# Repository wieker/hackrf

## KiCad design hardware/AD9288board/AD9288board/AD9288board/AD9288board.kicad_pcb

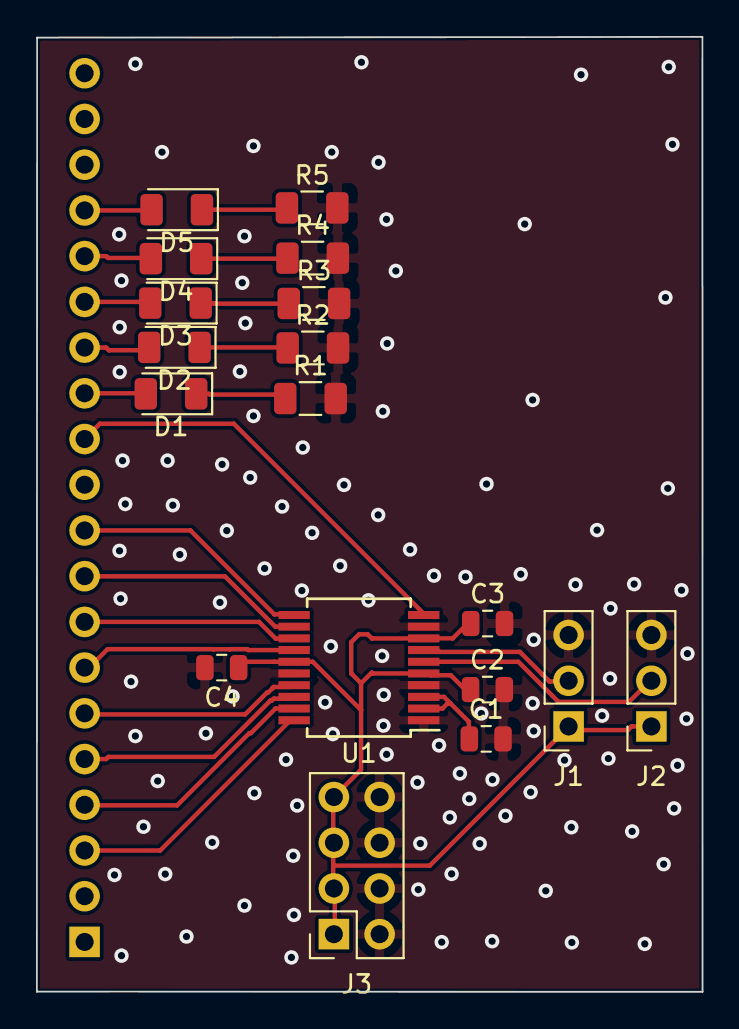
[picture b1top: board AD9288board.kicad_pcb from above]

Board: 2 copper layers, 37.0 x 53.0 mm, 19 parts (1 on the bottom side), 24 nets.

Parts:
C1, C2, C3, C4: 0.1uF; C_0805_2012Metric
D1, D2, D3, D4, D5: LED; LED_1206_3216Metric
J1, J2: Conn_01x03_Male; PinSocket_1x03_P2.54mm_Vertical
J3: Conn_02x04_Odd_Even; PinSocket_2x04_P2.54mm_Vertical
J4: Conn_01x20_Female; PinSocket_1x20_P2.54mm_Horizontal
R1, R2, R3, R4, R5: 10 kOhm; R_1206_3216Metric
U1: AD9283; SSOP-20_5.3x7.2mm_P0.65mm

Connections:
+3V3: C2.1, C3.1, C4.1, J1.1, J2.1, J3.1, J3.3, J3.5, J3.7, U1.5, U1.8, U1.15
GND: C1.2, C2.2, C3.2, C4.2, J1.3, J2.3, J3.2, J3.4, J3.6, J3.8, R1.2, R2.2, R3.2, R4.2, R5.2, U1.1, U1.4, U1.9, U1.16
unnamed: C1.1, U1.2, U1.3
unnamed: D1.1, R1.1
unnamed: D1.2, J4.13
unnamed: D2.1, R2.1
unnamed: D2.2, J4.14
unnamed: D3.1, R3.1
unnamed: D3.2, J4.15
unnamed: D4.1, R4.1
unnamed: D4.2, J4.16
unnamed: D5.1, R5.1
unnamed: D5.2, J4.17
unnamed: J1.2, U1.7
unnamed: J2.2, U1.6
unnamed: J4.3, U1.20
unnamed: J4.4, U1.19
unnamed: J4.5, U1.18
unnamed: J4.6, U1.17
unnamed: J4.7, U1.14
unnamed: J4.8, U1.13
unnamed: J4.9, U1.12
unnamed: J4.10, U1.11
unnamed: J4.12, U1.10

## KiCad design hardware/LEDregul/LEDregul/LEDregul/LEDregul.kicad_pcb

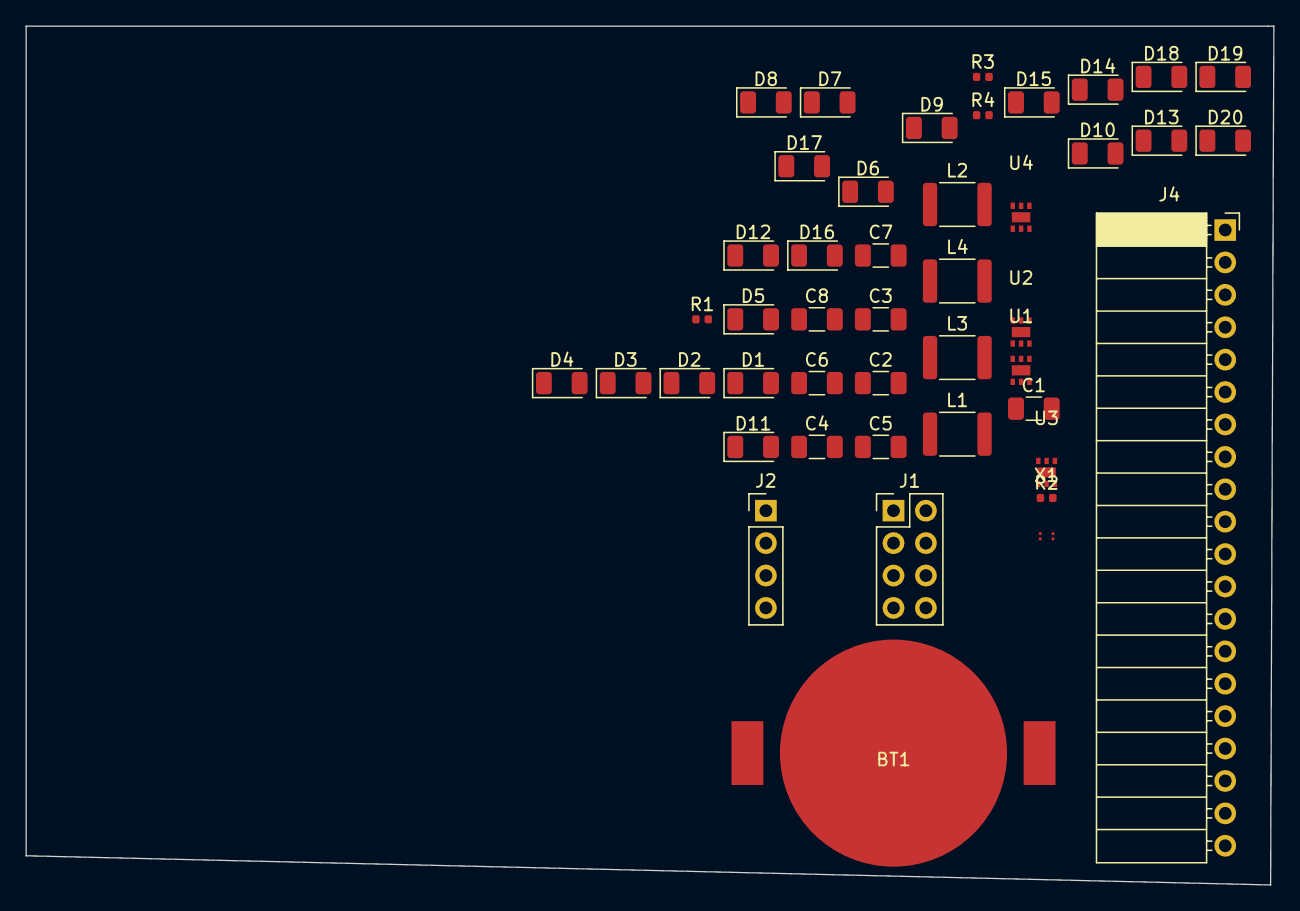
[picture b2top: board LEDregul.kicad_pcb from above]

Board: 2 copper layers, 97.8 x 67.3 mm, 45 parts (0 on the bottom side), 36 nets, no tracks yet.

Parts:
BT1: Battery_Cell; CR2032
C1, C3, C4, C7: 1uF; C_1206_3216Metric
C2, C5, C6, C8: 10uF; C_1206_3216Metric
D1, D2, D3, D4, D5, D6, D7, D8, D9, D10, D11, D12, D13, D14, D15, D16, D17, D18, D19, D20: LED; LED_1206_3216Metric
J1: Conn_02x04_Odd_Even; PinHeader_2x04_P2.54mm_Vertical
J2: Conn_01x04_Male; PinHeader_1x04_P2.54mm_Vertical
J4: Conn_01x20_Female; PinSocket_1x20_P2.54mm_Horizontal
L1, L2, L3, L4: L; L_1812_4532Metric
R1, R2, R3, R4: R; R_0402_1005Metric
U1, U2, U3, U4: FAN5341
X1: SiT1534

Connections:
+3V3: C2.1, C5.1, C6.1, C8.1, J1.2, J1.4, J1.6, J1.8, J2.3, J2.4, L1.1, L2.1, L3.1, L4.1, U1.2, U2.2, U3.2, U4.2, X1.4
C1: J4.8, U4.3
C2: J4.9, U3.3
C3: J4.10, U2.3
GND: BT1.2, C1.2, C2.2, C3.2, C4.2, C5.2, C6.2, C7.2, C8.2, J1.1, J1.3, J1.5, J1.7, R1.2, R2.2, R3.2, R4.2, U1.6, U2.6, U3.6, U4.6, X1.2
unnamed: BT1.1, J2.1, J2.2
unnamed: C1.1, D1.2, U1.1
unnamed: C3.1, D6.2, U2.1
unnamed: C4.1, D11.2, U3.1
unnamed: C7.1, D16.2, U4.1
unnamed: D1.1, D2.2
unnamed: D2.1, D3.2
unnamed: D3.1, D4.2
unnamed: D4.1, D5.2
unnamed: D5.1, R1.1, U1.4
unnamed: D6.1, D7.2
unnamed: D7.1, D8.2
unnamed: D8.1, D9.2
unnamed: D10.1, R2.1, U2.4
unnamed: D9.1, D10.2
unnamed: D11.1, D12.2
unnamed: D12.1, D13.2
unnamed: D13.1, D14.2
unnamed: D14.1, D15.2
unnamed: D15.1, R3.1, U3.4
unnamed: D16.1, D17.2
unnamed: D17.1, D18.2
unnamed: D18.1, D19.2
unnamed: D19.1, D20.2
unnamed: D20.1, R4.1, U4.4
unnamed: J4.11, X1.3
unnamed: J4.17, U1.3
unnamed: L1.2, U1.5
unnamed: L2.2, U2.5
unnamed: L3.2, U3.5
unnamed: L4.2, U4.5

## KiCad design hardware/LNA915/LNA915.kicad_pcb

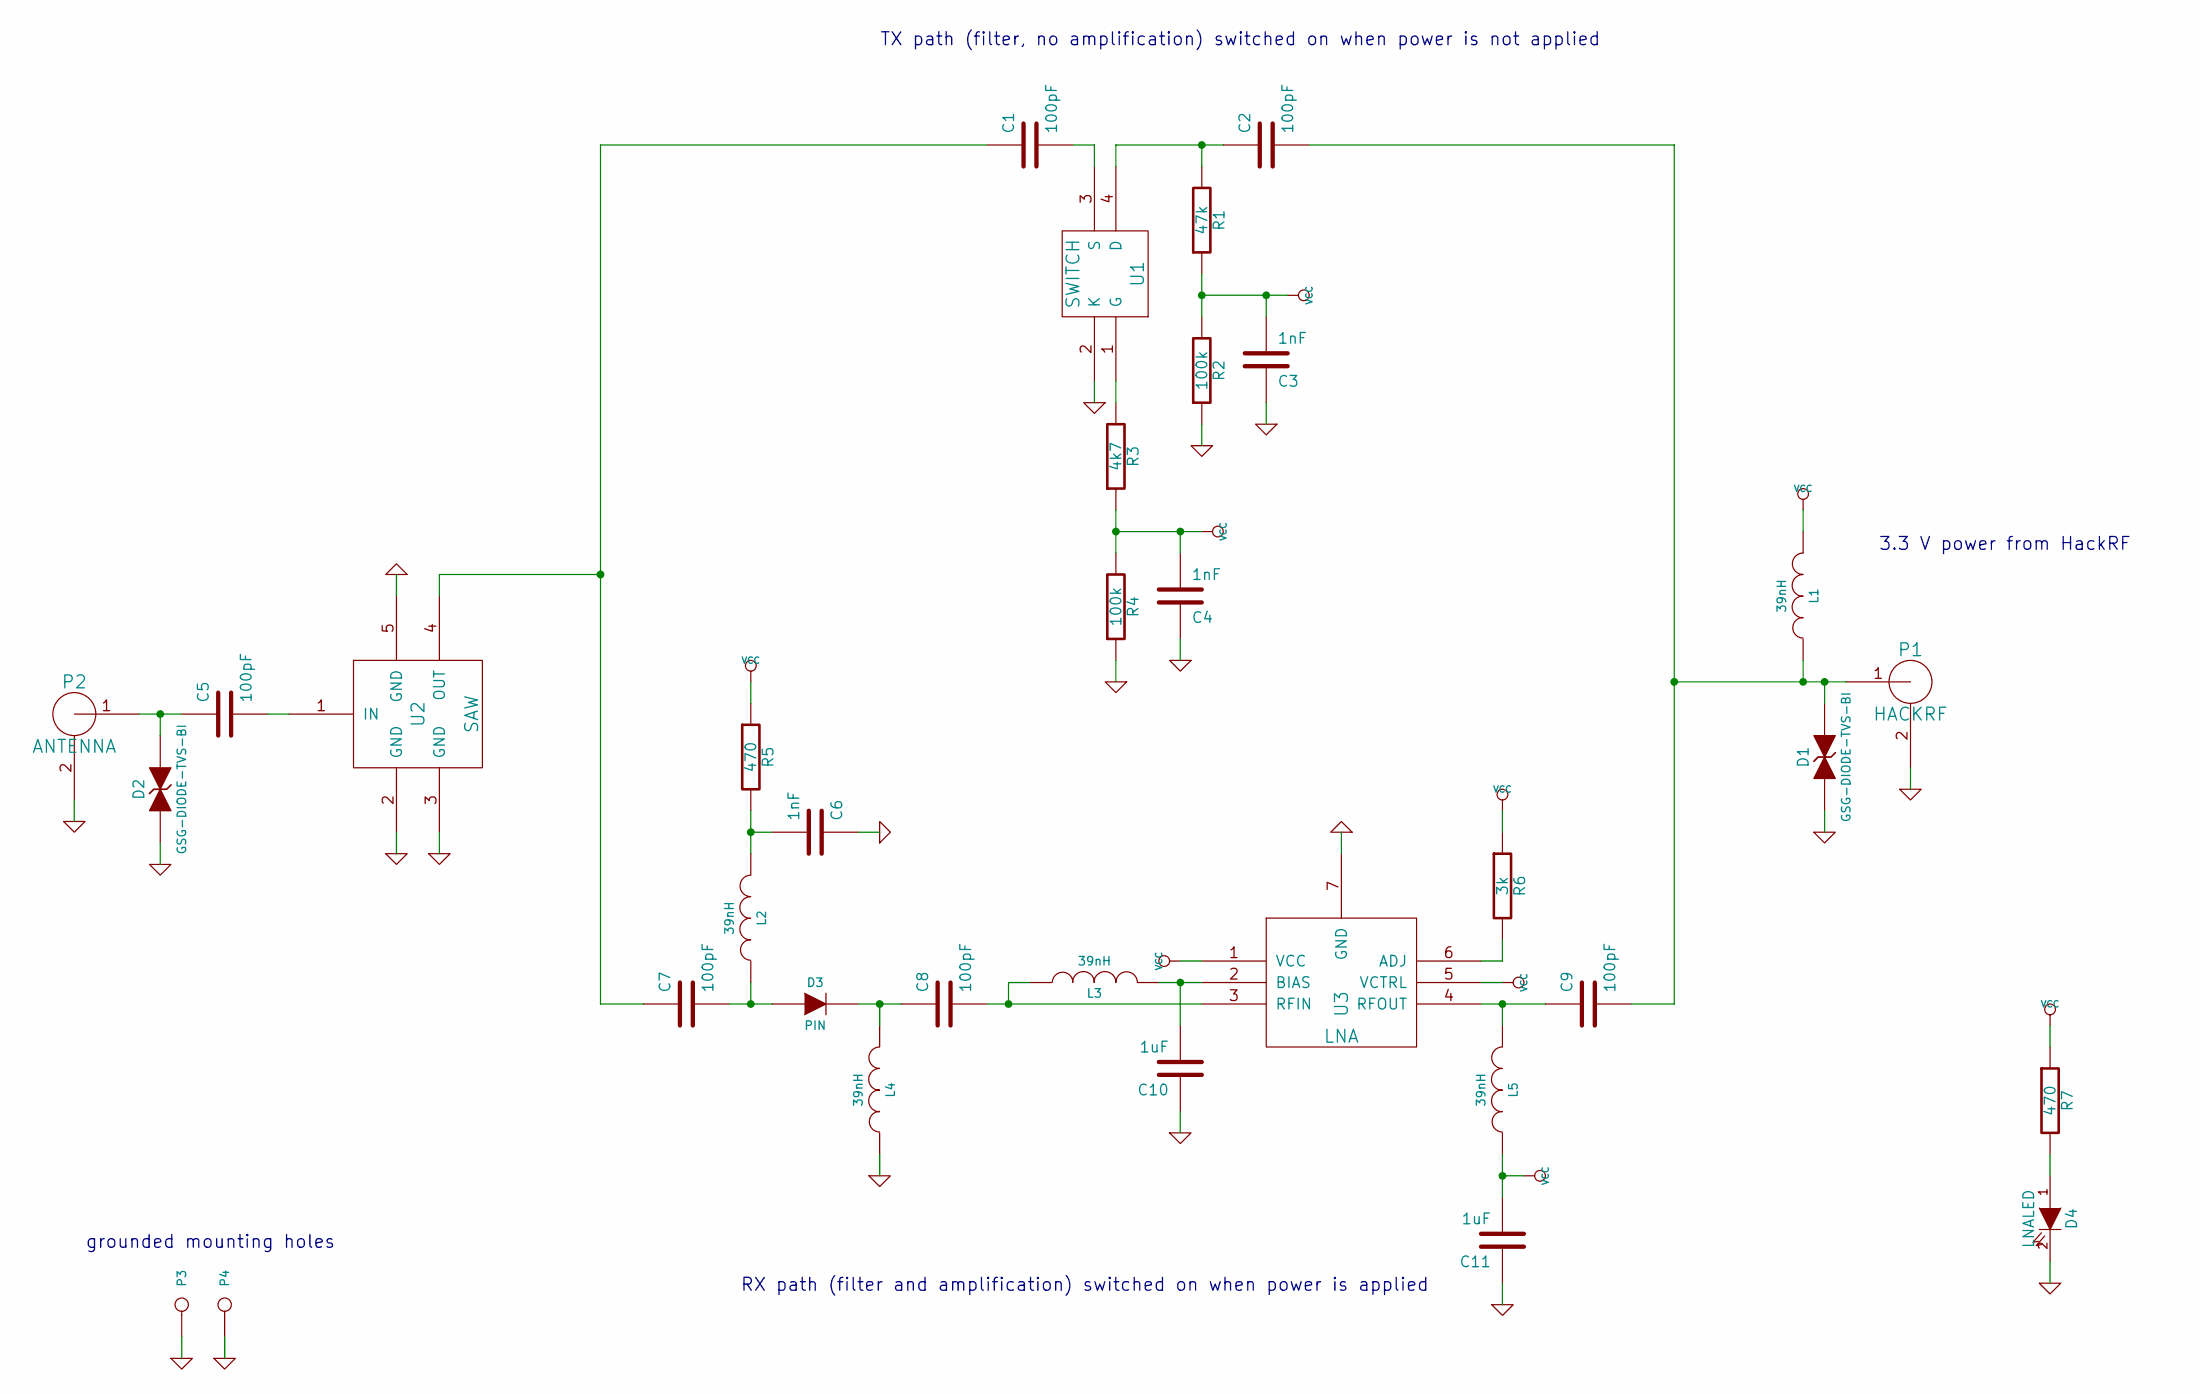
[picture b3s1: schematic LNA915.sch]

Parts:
C1, C2, C5, C7, C8, C9: 100pF; Part Number GRM1555C1H101JA01D
C3, C4, C6: 1nF; Part Number GRM155R71H102KA01D
C10, C11: 1uF; Part Number LMK105BJ105KV-F
D1, D2: GSG-DIODE-TVS-BI; Part Number LXES15AAA1-100
D3: PIN; Part Number BAP50-03
D4: LNALED; Part Number QTLP601C4TR
L1, L2, L3, L4, L5: 39nH; Part Number HK100539NJ-T
P1: HACKRF; Part Number CONSMA003.062
P2: ANTENNA; Part Number CONSMA003.062
P3, P4: CONN_1
R1: 47k; Part Number RMCF0402JT47K0
R2, R4: 100k; Part Number RMCF0402JT100K
R3: 4k7; Part Number RMCF0402JT4K70
R5, R7: 470; Part Number RMCF0402JT470R
R6: 3k; Part Number RMCF0402FT3K00
U1: SWITCH; Part Number BF1118,215
U2: SAW; Part Number FAR-F5QA-915M00-M2AK-J
U3: LNA; Part Number BGB 741L7ESD E6327

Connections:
GND: C3.1, C4.1, C6.1, C10.1, C11.1, D1.1 (A), D2.1 (A), D4.2 (K), L4.1, P1.2 (GND), P2.2 (GND), P3.1, P4.1, R2.1, R4.1, U1.2 (K), U2.2 (GND), U2.3 (GND), U2.5 (GND), U3.7 (GND)
unnamed: C8.1, D3.2 (K), L4.2
unnamed: C1.2, U1.3 (S)
unnamed: C2.1, R1.2, U1.4 (D)
unnamed: C7.2, D3.1 (A), L2.1
unnamed: R3.2, U1.1 (G)
unnamed: C5.1, D2.2 (K), P2.1 (RF)
unnamed: D4.1 (A), R7.2
unnamed: C1.1, C7.1, U2.4 (OUT)
unnamed: C6.2, L2.2, R5.2
unnamed: C5.2, U2.1 (IN)
unnamed: R6.2, U3.6 (ADJ)
unnamed: C2.2, C9.2, D1.2 (K), L1.1, P1.1 (RF)
unnamed: C9.1, L5.2, U3.4 (RFOUT)
unnamed: C8.2, L3.1, U3.3 (RFIN)
unnamed: C10.2, L3.2, U3.2 (BIAS)
VCC: C3.2, C4.2, C11.2, L1.2, L5.1, R1.1, R2.2, R3.1, R4.2, R5.1, R6.1, R7.1, U3.1 (VCC), U3.5 (VCTRL)

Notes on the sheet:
3.3 V power from HackRF
TX path (filter, no amplification) switched on when power is not applied
RX path (filter and amplification) switched on when power is applied
grounded mounting holes

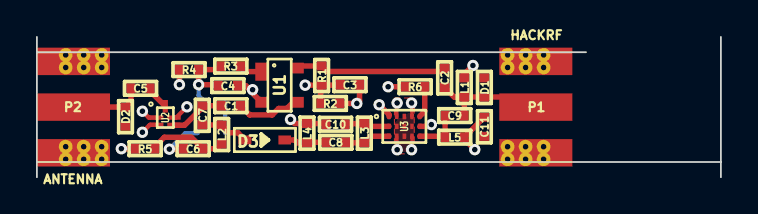
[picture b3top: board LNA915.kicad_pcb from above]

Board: 4 copper layers, 38.0 x 7.8 mm, 32 parts (0 on the bottom side), 17 nets.

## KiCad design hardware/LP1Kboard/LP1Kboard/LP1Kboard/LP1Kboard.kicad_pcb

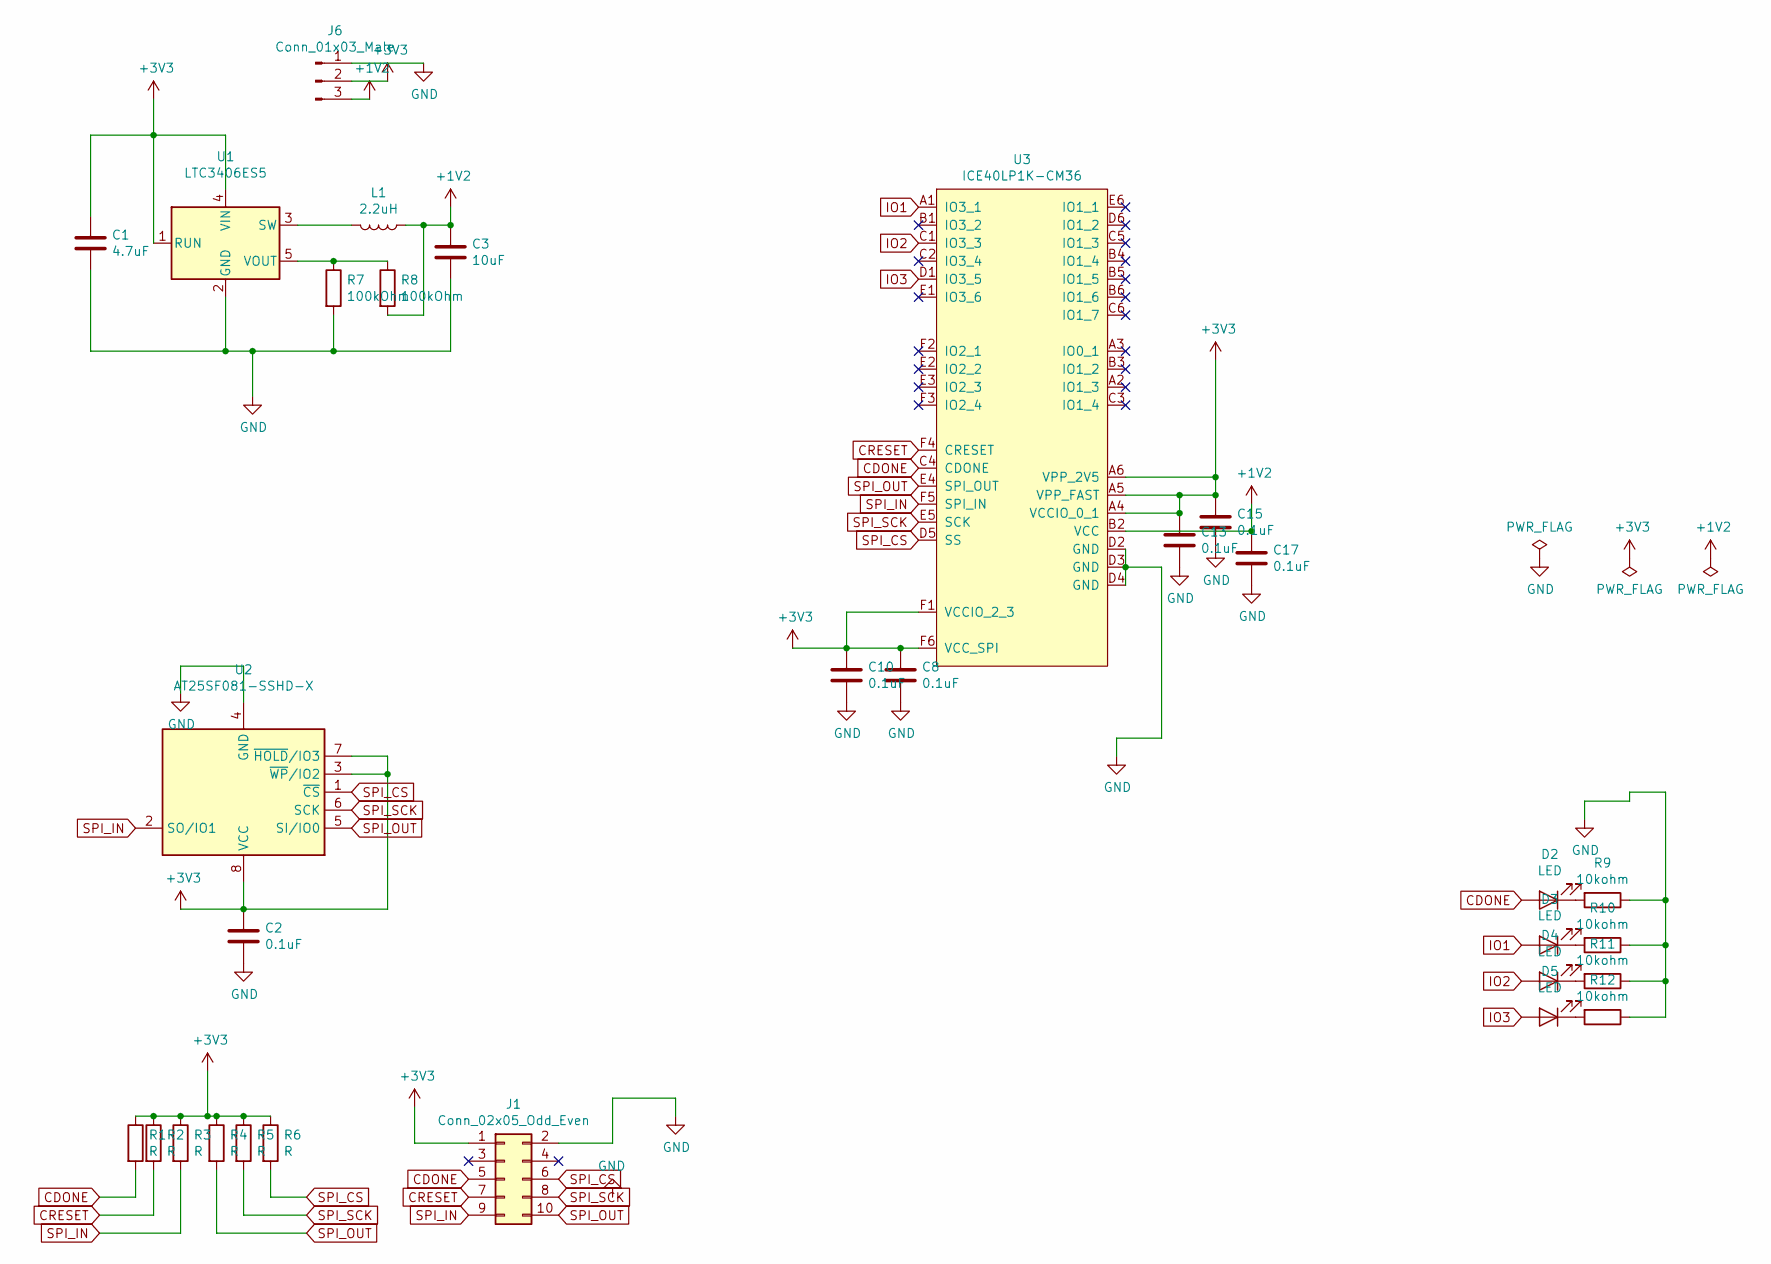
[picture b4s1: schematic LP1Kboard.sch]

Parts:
C1: 4.7uF; C_1206_3216Metric
C2, C8, C10, C13, C15, C17: 0.1uF; C_0805_2012Metric
C3: 10uF; C_1206_3216Metric
D2, D3, D4, D5: LED; LED_1206_3216Metric
J1: Conn_02x05_Odd_Even; PinHeader_2x05_P2.54mm_Vertical
J6: Conn_01x03_Male; PinHeader_1x03_P2.54mm_Vertical
L1: 2.2uH; L_1210_3225Metric
R1, R2, R3, R4, R5, R6: R; R_1206_3216Metric
R7, R8: 100kOhm; R_1206_3216Metric
R9, R10, R11, R12: 10kohm; R_1206_3216Metric
U1: LTC3406ES5; TSOT-23-5
U2: AT25SF081-SSHD-X; SOIC-8_3.9x4.9mm_P1.27mm
U3: ICE40LP1K-CM36; ice40-CM36-WLCSP-36_2.82x2.67mm_Layout6x6_P0.4mm

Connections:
+1V2: C3.1, C17.1, J6.3, L1.1, R8.2, U3.B2 (VCC)
+3V3: C1.1, C2.1, C8.1, C10.1, C13.1, C15.1, J1.1, J6.2, R1.1, R2.1, R3.1, R4.1, R5.1, R6.1, U1.1 (RUN), U1.4 (VIN), U2.3 (~WP~/IO2), U2.7 (~HOLD~/IO3), U2.8 (VCC), U3.A4 (VCCIO_0_1), U3.A5 (VPP_FAST), U3.A6 (VPP_2V5), U3.F1 (VCCIO_2_3), U3.F6 (VCC_SPI)
CDONE: D2.2 (A), J1.5, R1.2, U3.C4 (CDONE)
CRESET: J1.7, R2.2, U3.F4 (CRESET)
GND: C1.2, C2.2, C3.2, C8.2, C10.2, C13.2, C15.2, C17.2, J1.2, J6.1, R7.2, R9.1, R10.1, R11.1, R12.1, U1.2 (GND), U2.4 (GND), U3.D2 (GND), U3.D3 (GND), U3.D4 (GND)
IO1: D3.2 (A), U3.A1 (IO3_1)
IO2: D4.2 (A), U3.C1 (IO3_3)
IO3: D5.2 (A), U3.D1 (IO3_5)
unnamed: D2.1 (K), R9.2
unnamed: D3.1 (K), R10.2
unnamed: D4.1 (K), R11.2
unnamed: D5.1 (K), R12.2
unnamed: L1.2, U1.3 (SW)
unnamed: R7.1, R8.1, U1.5 (VOUT)
SPI_CS: J1.6, R6.2, U2.1 (~CS), U3.D5 (SS)
SPI_IN: J1.9, R3.2, U2.2 (SO/IO1), U3.F5 (SPI_IN)
SPI_OUT: J1.10, R4.2, U2.5 (SI/IO0), U3.E4 (SPI_OUT)
SPI_SCK: J1.8, R5.2, U2.6 (SCK), U3.E5 (SCK)

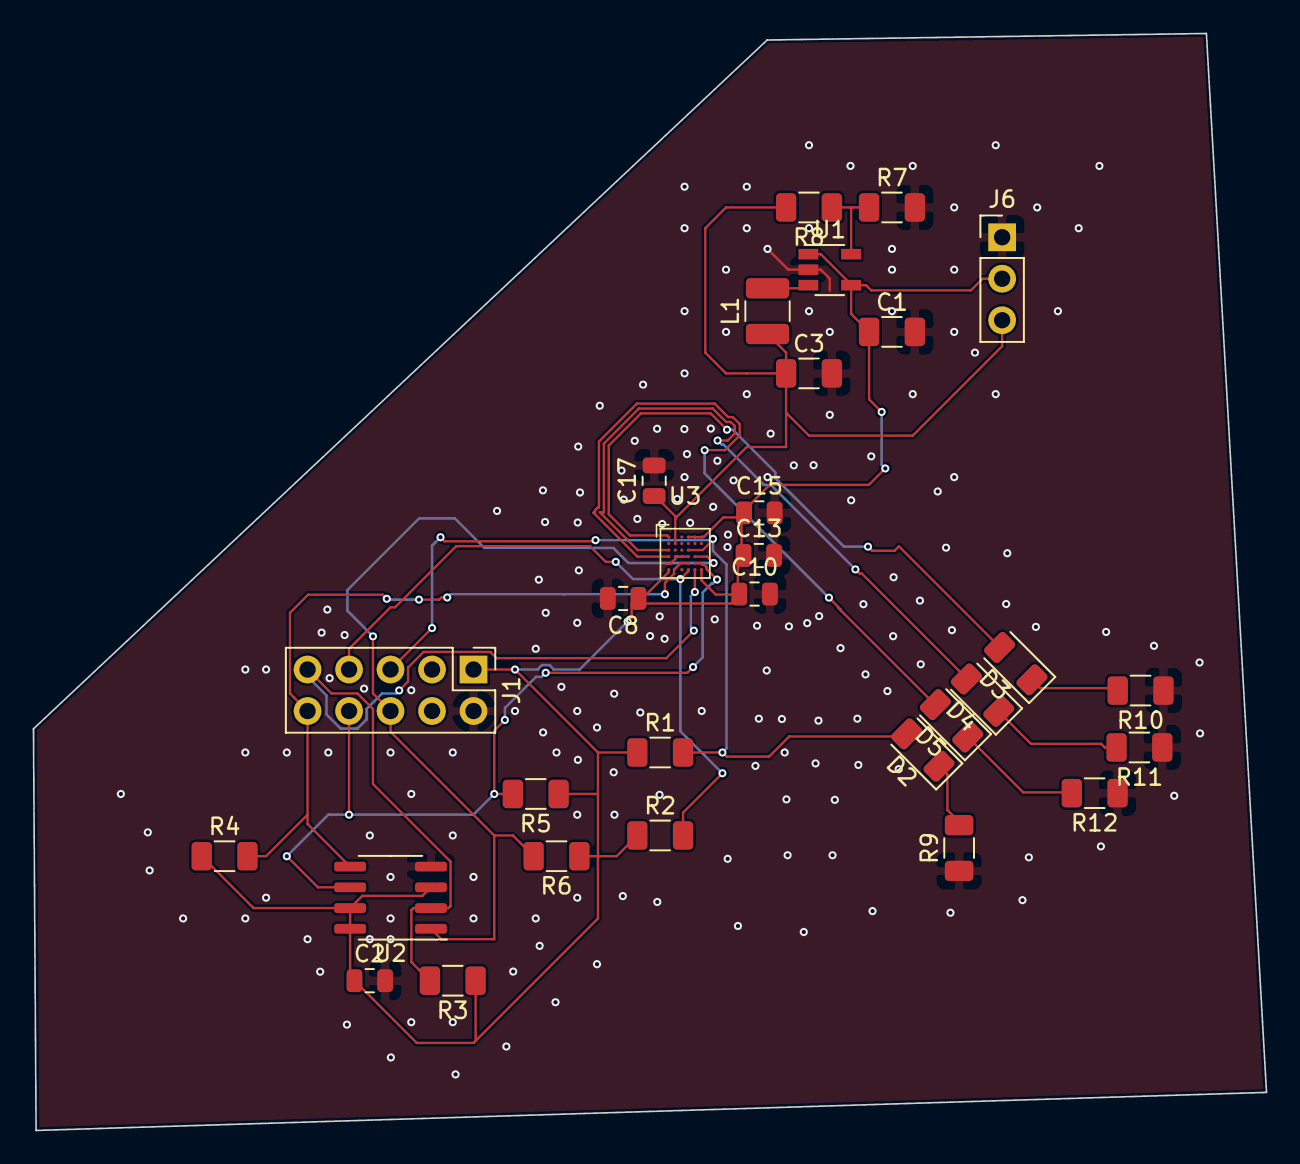
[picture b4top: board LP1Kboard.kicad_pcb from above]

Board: 2 copper layers, 75.5 x 67.2 mm, 30 parts (0 on the bottom side), 18 nets.

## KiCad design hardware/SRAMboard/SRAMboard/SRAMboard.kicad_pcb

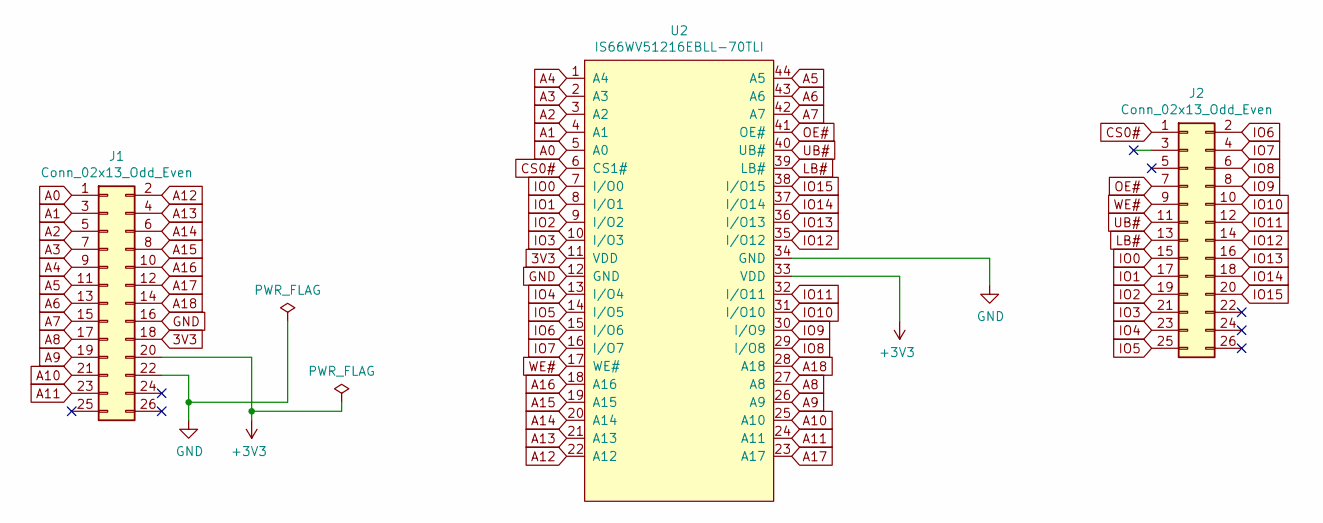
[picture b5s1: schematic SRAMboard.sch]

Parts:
J1, J2: Conn_02x13_Odd_Even; PinSocket_2x13_P2.54mm_Vertical
U2: IS66WV51216EBLL-70TLI; TSOP-II-44_10.16x18.41mm_P0.8mm

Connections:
3V3: J1.18, U2.11 (VDD)
+3V3: J1.20, U2.33 (VDD)
A0: J1.1, U2.5 (A0)
A1: J1.3, U2.4 (A1)
A2: J1.5, U2.3 (A2)
A3: J1.7, U2.2 (A3)
A4: J1.9, U2.1 (A4)
A5: J1.11, U2.44 (A5)
A6: J1.13, U2.43 (A6)
A7: J1.15, U2.42 (A7)
A8: J1.17, U2.27 (A8)
A9: J1.19, U2.26 (A9)
A10: J1.21, U2.25 (A10)
A11: J1.23, U2.24 (A11)
A12: J1.2, U2.22 (A12)
A13: J1.4, U2.21 (A13)
A14: J1.6, U2.20 (A14)
A15: J1.8, U2.19 (A15)
A16: J1.10, U2.18 (A16)
A17: J1.12, U2.23 (A17)
A18: J1.14, U2.28 (A18)
CS0#: J2.1, U2.6 (CS1#)
GND: J1.16, J1.22, U2.12 (GND), U2.34 (GND)
IO0: J2.15, U2.7 (I/O0)
IO1: J2.17, U2.8 (I/O1)
IO2: J2.19, U2.9 (I/O2)
IO3: J2.21, U2.10 (I/O3)
IO4: J2.23, U2.13 (I/O4)
IO5: J2.25, U2.14 (I/O5)
IO6: J2.2, U2.15 (I/O6)
IO7: J2.4, U2.16 (I/O7)
IO8: J2.6, U2.29 (I/O8)
IO9: J2.8, U2.30 (I/O9)
IO10: J2.10, U2.31 (I/O10)
IO11: J2.12, U2.32 (I/O11)
IO12: J2.14, U2.35 (I/O12)
IO13: J2.16, U2.36 (I/O13)
IO14: J2.18, U2.37 (I/O14)
IO15: J2.20, U2.38 (I/O15)
LB#: J2.13, U2.39 (LB#)
OE#: J2.7, U2.41 (OE#)
UB#: J2.11, U2.40 (UB#)
WE#: J2.9, U2.17 (WE#)

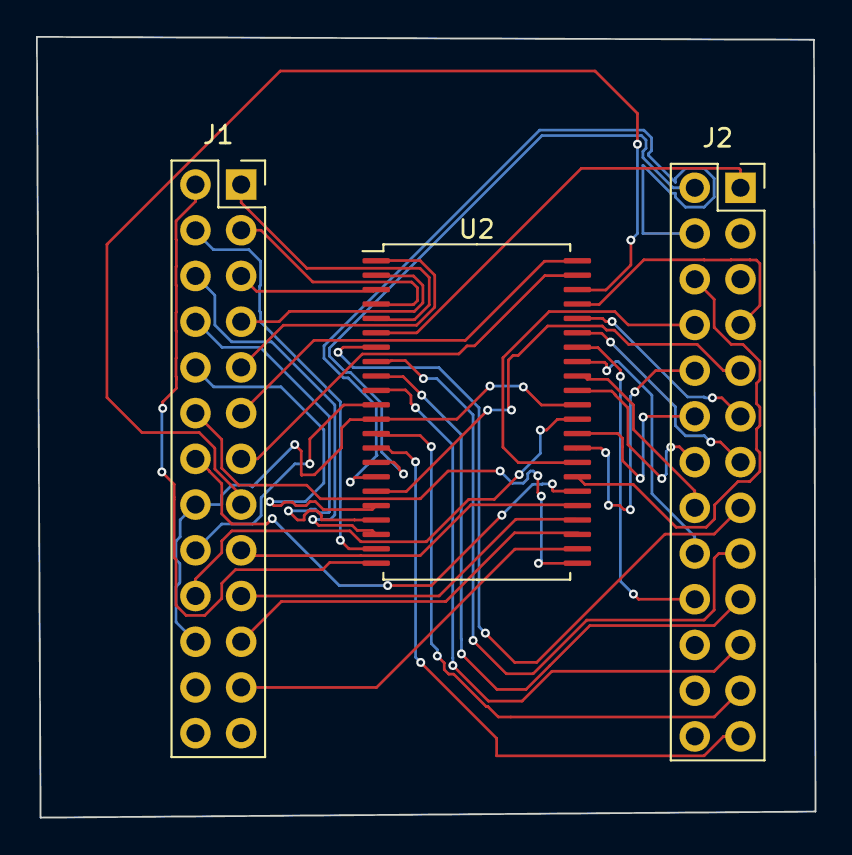
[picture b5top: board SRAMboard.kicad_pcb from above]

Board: 2 copper layers, 43.3 x 43.4 mm, 3 parts (0 on the bottom side), 43 nets.

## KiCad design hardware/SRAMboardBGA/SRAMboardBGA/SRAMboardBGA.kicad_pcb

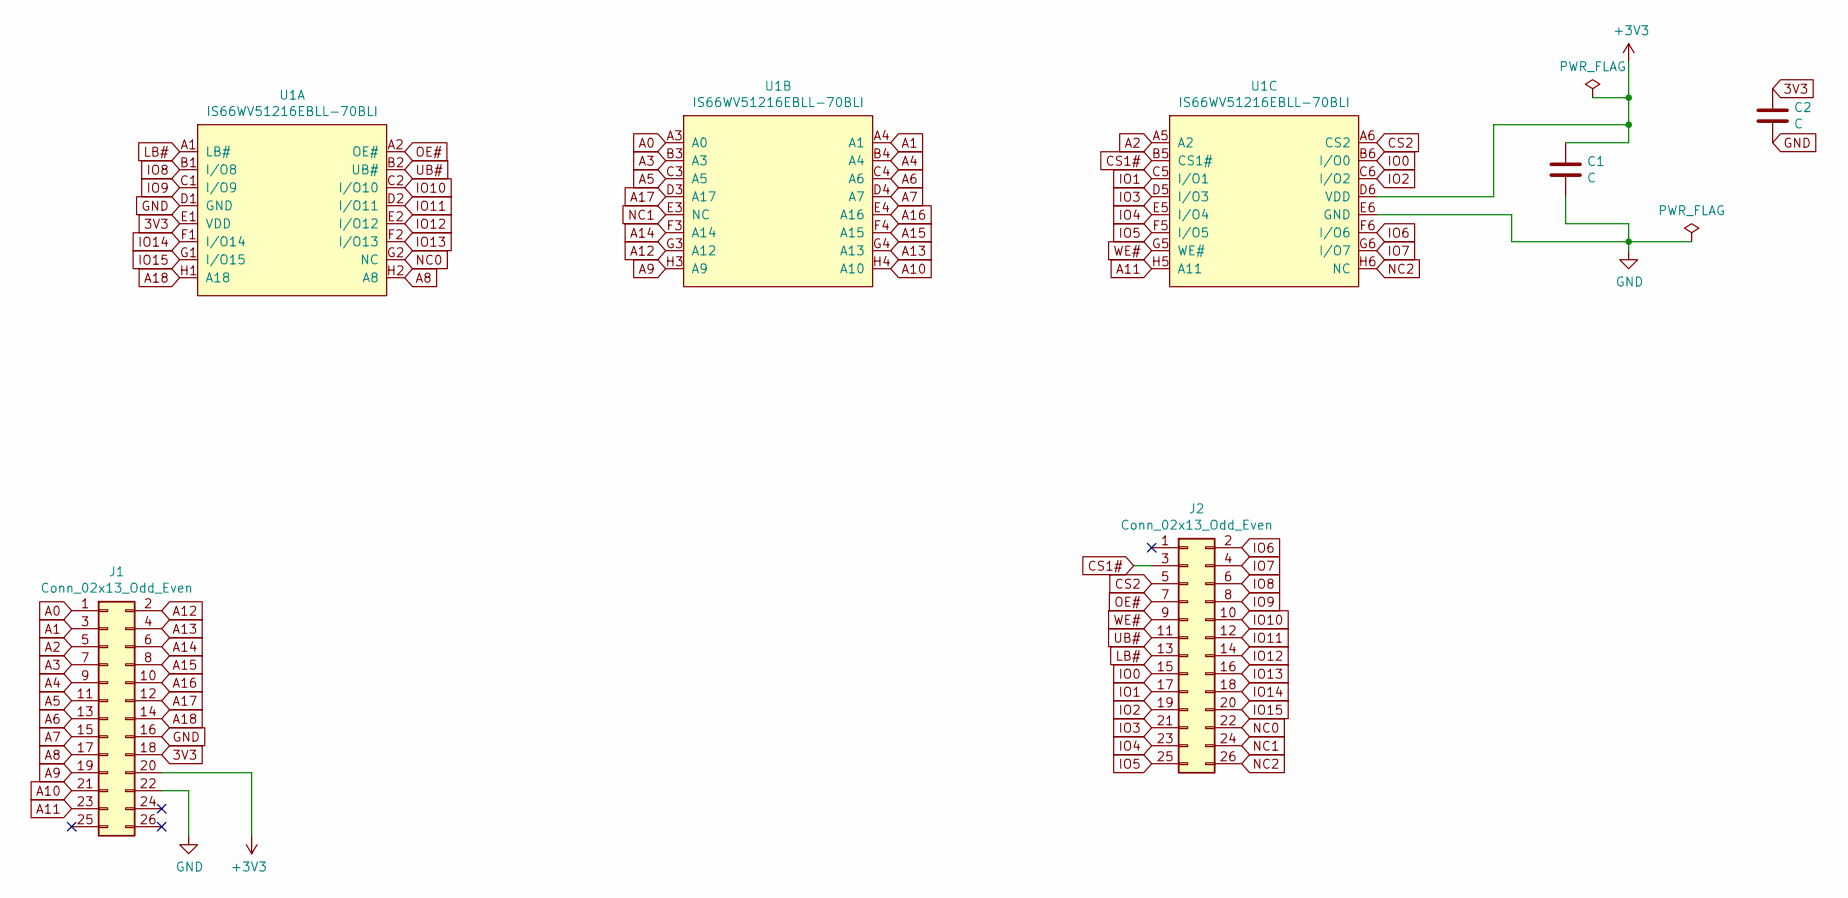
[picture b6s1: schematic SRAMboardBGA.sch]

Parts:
C1, C2: C; C_0805_2012Metric
J1, J2: Conn_02x13_Odd_Even; PinSocket_2x13_P2.54mm_Vertical
U1: IS66WV51216EBLL-70BLI; BGA-48_6.0x8.0mm_Layout6x8_P0.75mm

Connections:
3V3: C2.1, J1.18, U1.E1 (VDD)
+3V3: C1.1, J1.20, U1.D6 (VDD)
A0: J1.1, U1.A3 (A0)
A1: J1.3, U1.A4 (A1)
A2: J1.5, U1.A5 (A2)
A3: J1.7, U1.B3 (A3)
A4: J1.9, U1.B4 (A4)
A5: J1.11, U1.C3 (A5)
A6: J1.13, U1.C4 (A6)
A7: J1.15, U1.D4 (A7)
A8: J1.17, U1.H2 (A8)
A9: J1.19, U1.H3 (A9)
A10: J1.21, U1.H4 (A10)
A11: J1.23, U1.H5 (A11)
A12: J1.2, U1.G3 (A12)
A13: J1.4, U1.G4 (A13)
A14: J1.6, U1.F3 (A14)
A15: J1.8, U1.F4 (A15)
A16: J1.10, U1.E4 (A16)
A17: J1.12, U1.D3 (A17)
A18: J1.14, U1.H1 (A18)
CS1#: J2.3, U1.B5 (CS1#)
CS2: J2.5, U1.A6 (CS2)
GND: C1.2, C2.2, J1.16, J1.22, U1.D1 (GND), U1.E6 (GND)
IO0: J2.15, U1.B6 (I/O0)
IO1: J2.17, U1.C5 (I/O1)
IO2: J2.19, U1.C6 (I/O2)
IO3: J2.21, U1.D5 (I/O3)
IO4: J2.23, U1.E5 (I/O4)
IO5: J2.25, U1.F5 (I/O5)
IO6: J2.2, U1.F6 (I/O6)
IO7: J2.4, U1.G6 (I/O7)
IO8: J2.6, U1.B1 (I/O8)
IO9: J2.8, U1.C1 (I/O9)
IO10: J2.10, U1.C2 (I/O10)
IO11: J2.12, U1.D2 (I/O11)
IO12: J2.14, U1.E2 (I/O12)
IO13: J2.16, U1.F2 (I/O13)
IO14: J2.18, U1.F1 (I/O14)
IO15: J2.20, U1.G1 (I/O15)
LB#: J2.13, U1.A1 (LB#)
NC0: J2.22, U1.G2 (NC)
NC1: J2.24, U1.E3 (NC)
NC2: J2.26, U1.H6 (NC)
OE#: J2.7, U1.A2 (OE#)
UB#: J2.11, U1.B2 (UB#)
WE#: J2.9, U1.G5 (WE#)

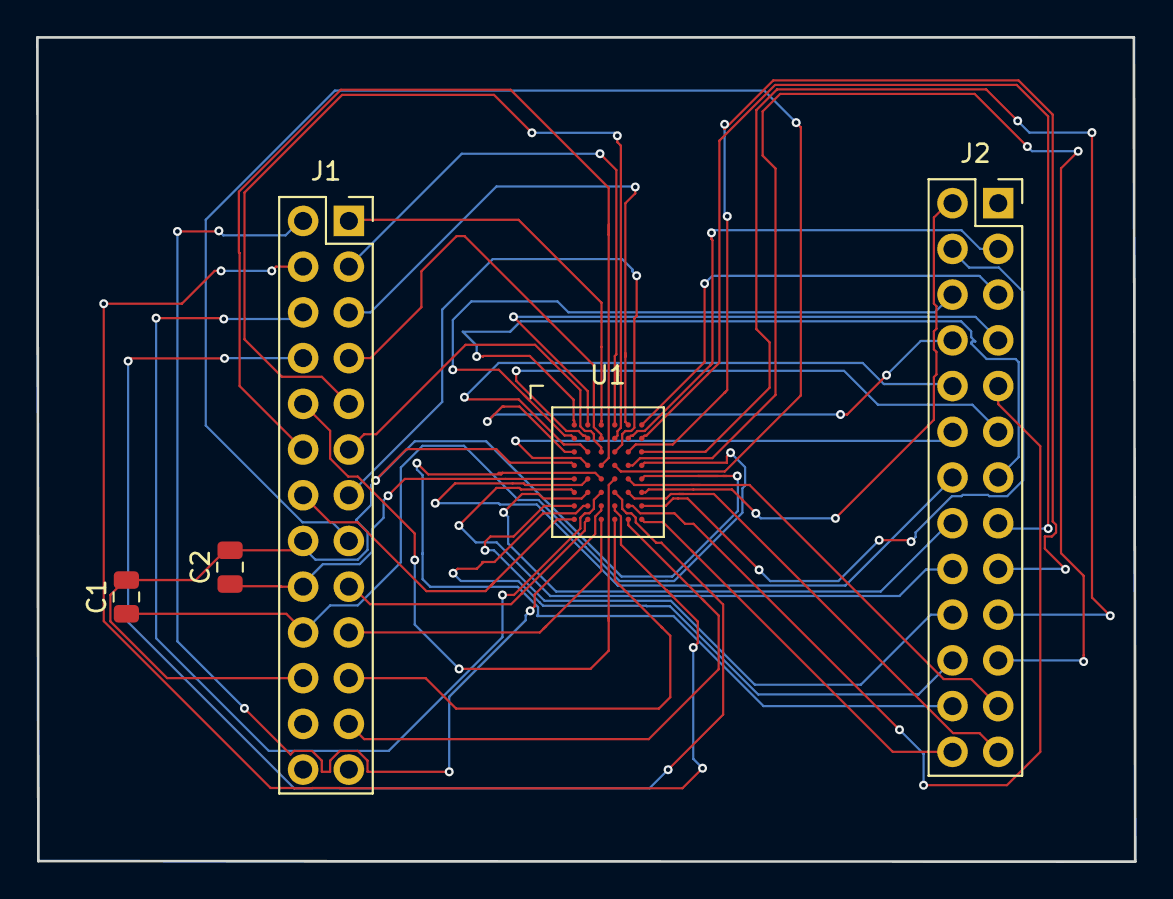
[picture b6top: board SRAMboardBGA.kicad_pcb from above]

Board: 4 copper layers, 61.0 x 45.8 mm, 5 parts (0 on the bottom side), 47 nets.

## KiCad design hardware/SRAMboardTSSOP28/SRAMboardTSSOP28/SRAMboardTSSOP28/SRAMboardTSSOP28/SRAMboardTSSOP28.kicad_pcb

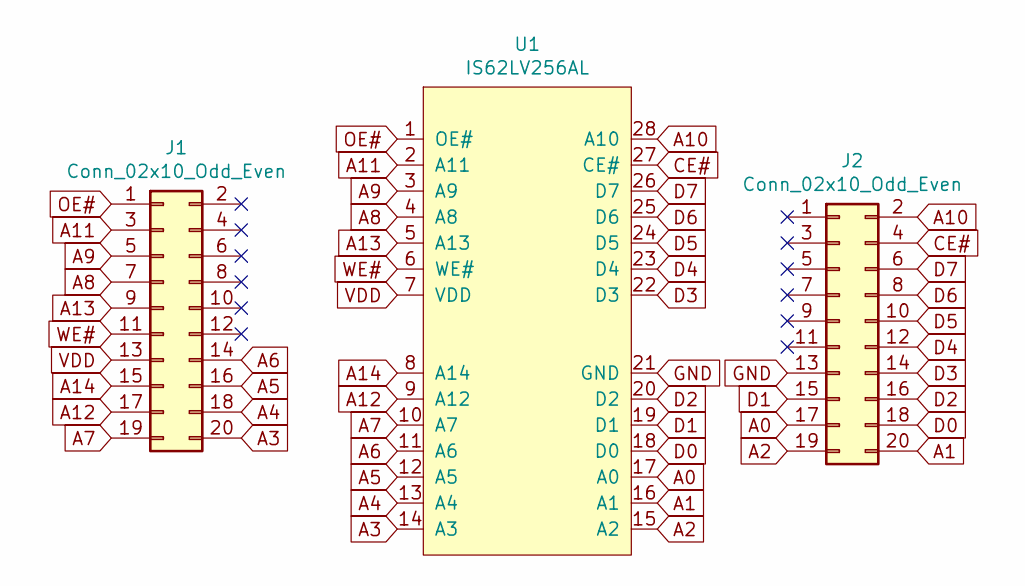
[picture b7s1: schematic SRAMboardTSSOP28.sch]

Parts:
J1, J2: Conn_02x10_Odd_Even; PinHeader_2x10_P2.54mm_Vertical
U1: IS62LV256AL; TSOP-I-28_11.8x8mm_P0.55mm

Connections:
A0: J2.17, U1.17 (A0)
A1: J2.20, U1.16 (A1)
A2: J2.19, U1.15 (A2)
A3: J1.20, U1.14 (A3)
A4: J1.18, U1.13 (A4)
A5: J1.16, U1.12 (A5)
A6: J1.14, U1.11 (A6)
A7: J1.19, U1.10 (A7)
A8: J1.7, U1.4 (A8)
A9: J1.5, U1.3 (A9)
A10: J2.2, U1.28 (A10)
A11: J1.3, U1.2 (A11)
A12: J1.17, U1.9 (A12)
A13: J1.9, U1.5 (A13)
A14: J1.15, U1.8 (A14)
CE#: J2.4, U1.27 (CE#)
D0: J2.18, U1.18 (D0)
D1: J2.15, U1.19 (D1)
D2: J2.16, U1.20 (D2)
D3: J2.14, U1.22 (D3)
D4: J2.12, U1.23 (D4)
D5: J2.10, U1.24 (D5)
D6: J2.8, U1.25 (D6)
D7: J2.6, U1.26 (D7)
GND: J2.13, U1.21 (GND)
OE#: J1.1, U1.1 (OE#)
VDD: J1.13, U1.7 (VDD)
WE#: J1.11, U1.6 (WE#)

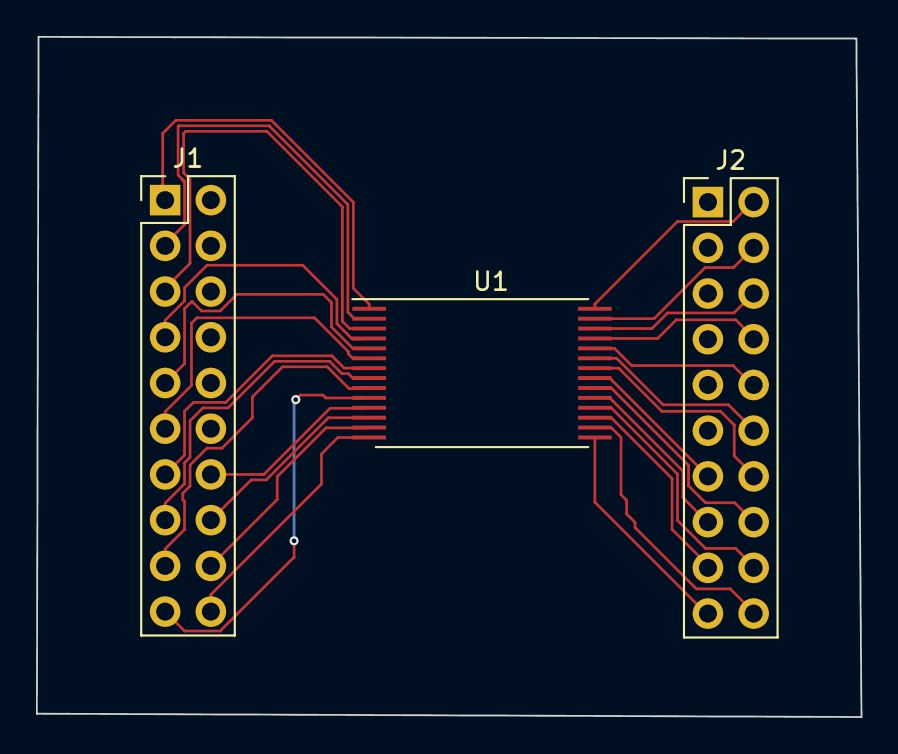
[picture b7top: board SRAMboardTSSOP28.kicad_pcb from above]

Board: 2 copper layers, 45.8 x 37.8 mm, 3 parts (0 on the bottom side), 28 nets.
